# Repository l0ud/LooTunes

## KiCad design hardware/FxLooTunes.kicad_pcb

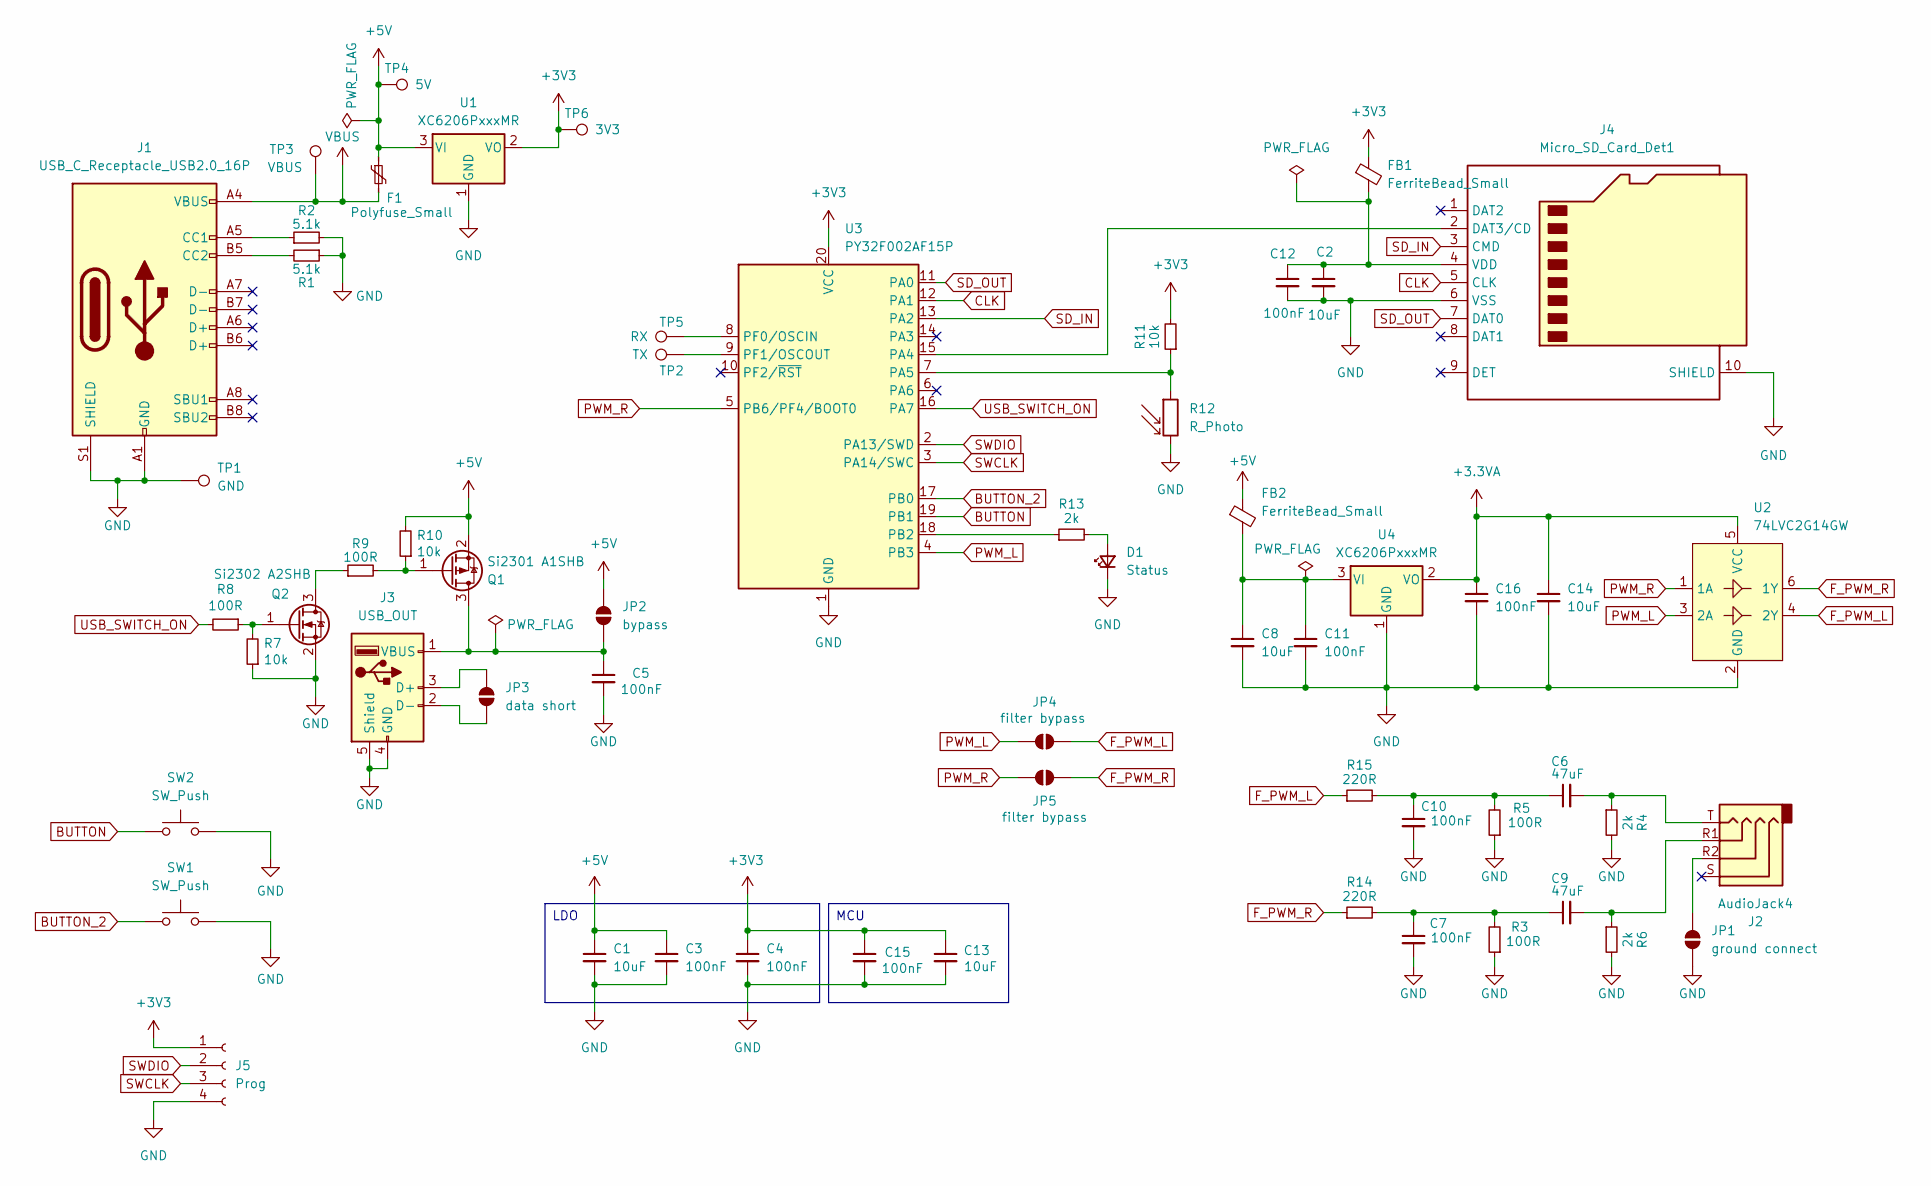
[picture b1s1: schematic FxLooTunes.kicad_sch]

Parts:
C1, C2, C8, C13, C14: 10uF; C_0402_1005Metric
C3, C4, C5, C7, C10, C11, C12, C15, C16: 100nF; C_0402_1005Metric
C6, C9: 47uF; C_0805_2012Metric
D1: Status; LED_0402_1005Metric
F1: Polyfuse_Small; Fuse_1206_3216Metric
FB1, FB2: FerriteBead_Small; L_0603_1608Metric
J1: USB_C_Receptacle_USB2.0_16P; USB_C_Receptacle_HCTL_HC-TYPE-C-16P-01A
J2: AudioJack4; PJ-322
J3: USB_OUT; USB_A_Connfly_DS1095
J4: Micro_SD_Card_Det1; GCT-MEM2055-00-190-01-A
J5: Prog; PinHeader_1x04_P1.27mm_Vertical
JP1: ground connect; SolderJumper-2_P1.3mm_Open_TrianglePad1.0x1.5mm
JP2: bypass; SolderJumper-2_P1.3mm_Open_TrianglePad1.0x1.5mm
JP3: data short; SolderJumper-2_P1.3mm_Open_TrianglePad1.0x1.5mm
JP4, JP5: filter bypass; SolderJumper-2_P1.3mm_Open_TrianglePad1.0x1.5mm
Q1: Si2301 A1SHB; SOT-23
Q2: Si2302 A2SHB; SOT-23
R1, R2: 5.1k; R_0402_1005Metric
R3, R5, R8, R9: 100R; R_0402_1005Metric
R4, R6, R13: 2k; R_0402_1005Metric
R7, R10, R11: 10k; R_0402_1005Metric
R12: R_Photo; R_LDR_5.0x4.1mm_P3mm_Vertical
R14, R15: 220R; R_0402_1005Metric
SW1, SW2: SW_Push; SW_SPST_TL3342
TP1: GND; TestPoint_Pad_D1.5mm
TP2: TX; TestPoint_Pad_D1.5mm
TP3: VBUS; TestPoint_Pad_D1.5mm
TP4: 5V; TestPoint_Pad_D1.5mm
TP5: RX; TestPoint_Pad_D1.5mm
TP6: 3V3; TestPoint_Pad_D1.5mm
U1, U4: XC6206PxxxMR; SOT-23-3
U2: 74LVC2G14GW; SOT-363_SC-70-6
U3: PY32F002AF15P; TSSOP-20_4.4x6.5mm_P0.65mm

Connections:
+3.3VA: C14.1, C16.1, U2.5 (VCC), U4.2 (VO)
+3V3: C4.1, C13.1, C15.1, FB1.1, J5.1, R11.2, TP6.1, U1.2 (VO), U3.20 (VCC)
BUTTON: SW2.1, U3.19 (PB1)
BUTTON_2: SW1.1, U3.17 (PB0)
CLK: J4.5 (CLK), U3.12 (PA1)
F_PWM_L: JP4.2 (B), R15.1, U2.4 (2Y)
F_PWM_R: JP5.2 (B), R14.1, U2.6 (1Y)
GND: C1.2, C2.2, C3.2, C4.2, C5.2, C7.2, C8.2, C10.2, C11.2, C12.2, C13.2, C14.2, C15.2, C16.2, D1.1 (K), J1.A1 (GND), J1.A12 (GND), J1.B1 (GND), J1.B12 (GND), J1.S1 (SHIELD), J3.4 (GND), J3.5 (Shield), J4.6 (VSS), J4.10 (SHIELD), J5.4, JP1.2 (B), Q2.2 (S), R1.1, R2.2, R3.1, R4.2, R5.1, R6.2, R7.1, R12.2, SW1.2, SW2.2, TP1.1, U1.1 (GND), U2.2 (GND), U3.1 (GND), U4.1 (GND)
unnamed: C6.1, C10.1, R5.2, R15.2
unnamed: C6.2, J2.T, R4.1
unnamed: C7.1, C9.1, R3.2, R14.2
unnamed: C9.2, J2.R1, R6.1
unnamed: D1.2 (A), R13.2
unnamed: J1.A5 (CC1), R2.1
unnamed: J1.B5 (CC2), R1.2
unnamed: J3.3 (D+), JP3.1 (A)
unnamed: J3.2 (D-), JP3.2 (B)
unnamed: J4.2 (DAT3/CD), U3.15 (PA4)
unnamed: C2.1, C12.1, FB1.2, J4.4 (VDD)
unnamed: J2.R2, JP1.1 (A)
unnamed: Q2.3 (D), R9.1
unnamed: Q2.1 (G), R7.2, R8.1
unnamed: Q1.1 (G), R9.2, R10.1
unnamed: R11.1, R12.1, U3.7 (PA5)
unnamed: R13.1, U3.18 (PB2)
unnamed: TP5.1, U3.8 (PF0/OSCIN)
unnamed: TP2.1, U3.9 (PF1/OSCOUT)
PWM_L: JP4.1 (A), U2.3 (2A), U3.4 (PB3)
PWM_R: JP5.1 (A), U2.1 (1A), U3.5 (PB6/PF4/BOOT0)
SD_IN: J4.3 (CMD), U3.13 (PA2)
SD_OUT: J4.7 (DAT0), U3.11 (PA0)
SWCLK: J5.3, U3.3 (PA14/SWC)
SWDIO: J5.2, U3.2 (PA13/SWD)
USB_SWITCH_IN: R8.2, U3.16 (PA7)
VBUS: F1.2, J1.A4 (VBUS), J1.A9 (VBUS), J1.B4 (VBUS), J1.B9 (VBUS), TP3.1

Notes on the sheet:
LDO
MCU

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
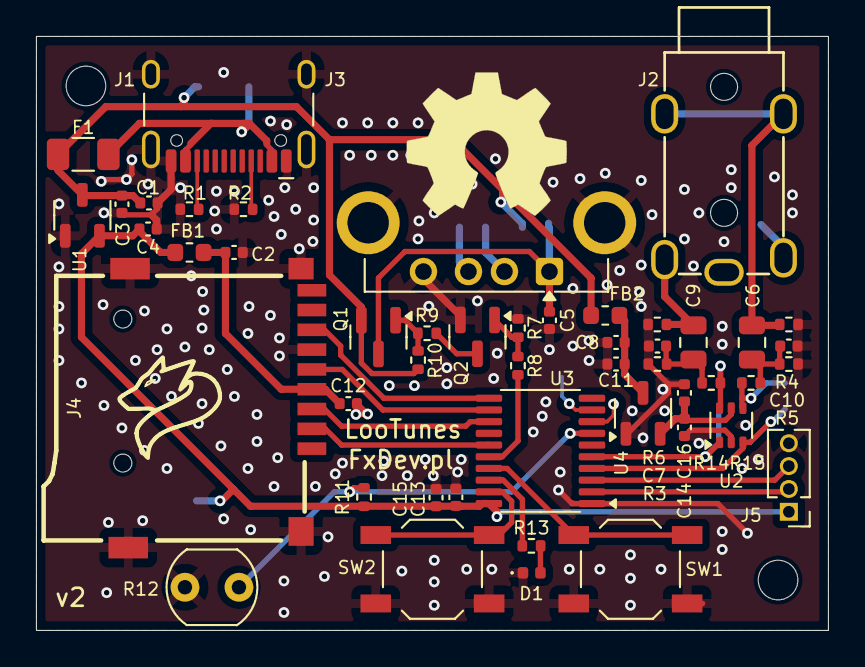
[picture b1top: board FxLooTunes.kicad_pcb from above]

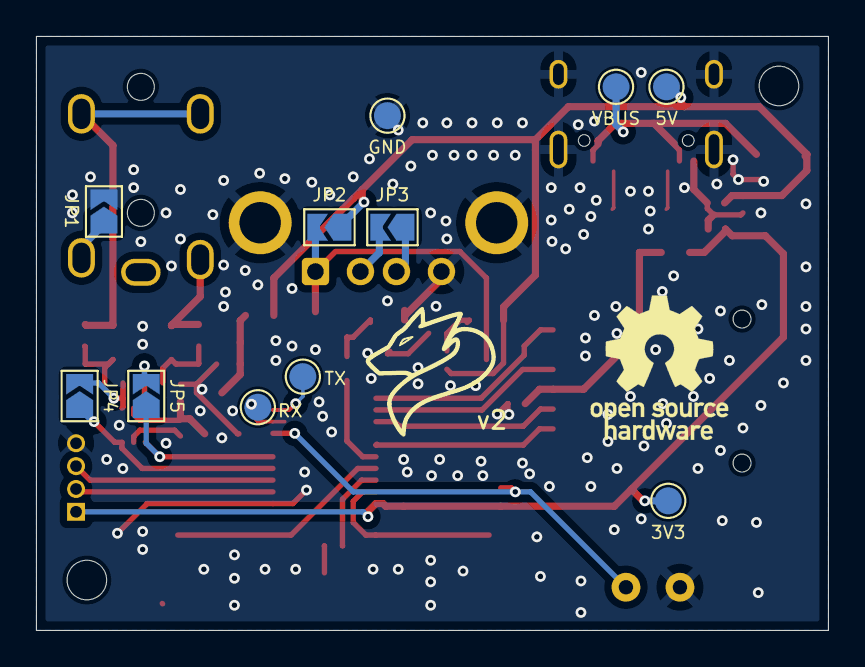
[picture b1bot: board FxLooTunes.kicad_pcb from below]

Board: 2 copper layers, 44.0 x 33.0 mm, 59 parts (11 on the bottom side), 38 nets.

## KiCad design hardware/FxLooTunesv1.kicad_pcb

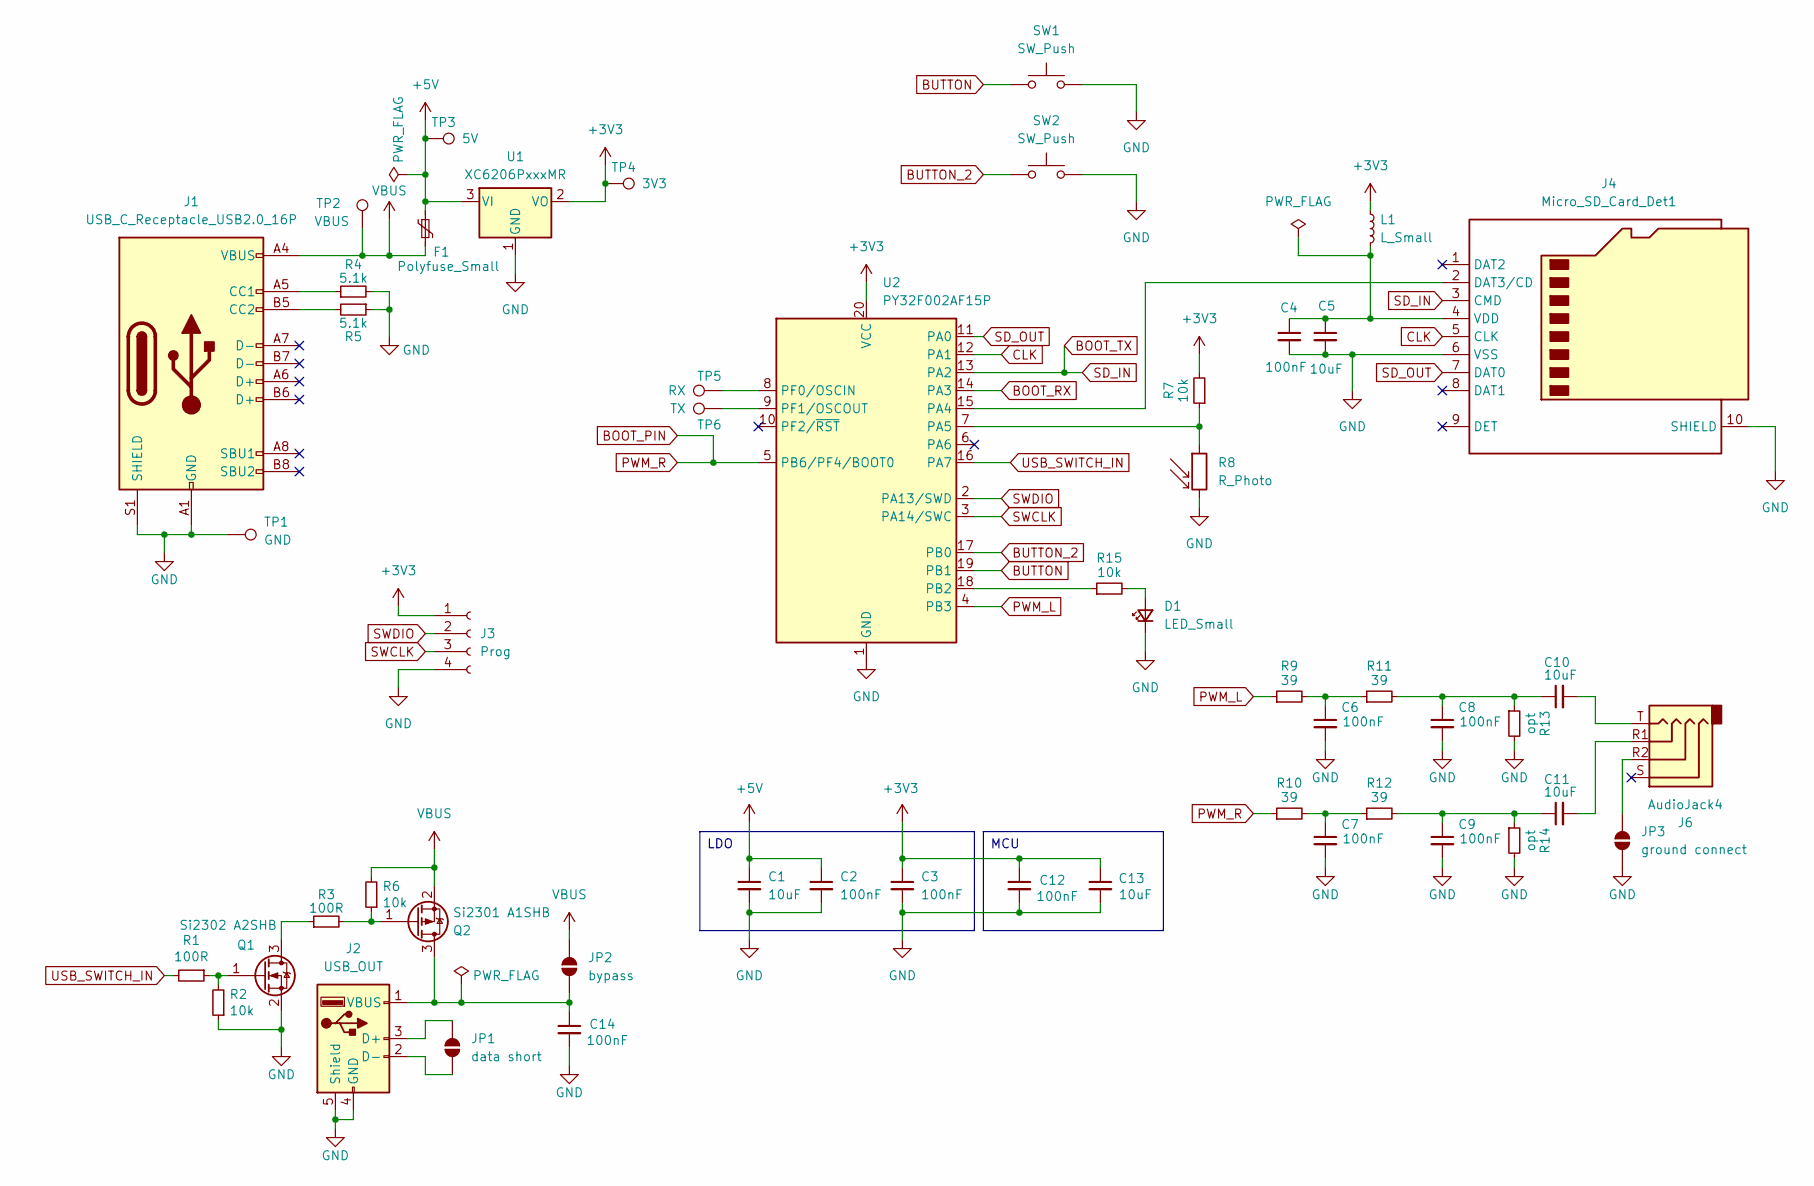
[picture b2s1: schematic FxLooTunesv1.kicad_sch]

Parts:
C1, C5, C10, C11, C13: 10uF; C_0402_1005Metric
C2, C3, C4, C6, C7, C8, C9, C12, C14: 100nF; C_0402_1005Metric
D1: LED_Small; LED_0402_1005Metric
F1: Polyfuse_Small; Fuse_1206_3216Metric
J1: USB_C_Receptacle_USB2.0_16P; USB_C_Receptacle_HCTL_HC-TYPE-C-16P-01A
J2: USB_OUT; USB_A_Connfly_DS1095
J3: Prog; PinHeader_1x04_P1.27mm_Vertical
J4: Micro_SD_Card_Det1; GCT-MEM2055-00-190-01-A
J6: AudioJack4; PJ-322
JP1: data short; SolderJumper-2_P1.3mm_Open_TrianglePad1.0x1.5mm
JP2: bypass; SolderJumper-2_P1.3mm_Open_TrianglePad1.0x1.5mm
JP3: ground connect; SolderJumper-2_P1.3mm_Open_TrianglePad1.0x1.5mm
L1: L_Small; L_0402_1005Metric
Q1: Si2302 A2SHB; SOT-23
Q2: Si2301 A1SHB; SOT-23
R1, R3: 100R; R_0402_1005Metric
R2, R6, R7, R15: 10k; R_0402_1005Metric
R4, R5: 5.1k; R_0402_1005Metric
R8: R_Photo; R_LDR_5.0x4.1mm_P3mm_Vertical
R9, R10, R11, R12: 39; R_0402_1005Metric
R13, R14: opt; R_0402_1005Metric
SW1, SW2: SW_Push; SW_SPST_TL3342
TP1: GND; TestPoint_Pad_D1.5mm
TP2: VBUS; TestPoint_Pad_D1.5mm
TP3: 5V; TestPoint_Pad_D1.5mm
TP4: 3V3; TestPoint_Pad_D1.5mm
TP5: RX; TestPoint_Pad_D1.5mm
TP6: TX; TestPoint_Pad_D1.5mm
U1: XC6206PxxxMR; SOT-23-3
U2: PY32F002AF15P; TSSOP-20_4.4x6.5mm_P0.65mm

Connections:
+3V3: C3.1, C12.1, C13.1, J3.1, L1.1, R7.2, TP4.1, U1.2 (VO), U2.20 (VCC)
BOOT_PIN: R10.1, U2.5 (PB6/PF4/BOOT0)
BOOT_RX: U2.14 (PA3)
BOOT_TX: J4.3 (CMD), U2.13 (PA2)
BUTTON: SW1.1, U2.19 (PB1)
BUTTON_2: SW2.1, U2.17 (PB0)
CLK: J4.5 (CLK), U2.12 (PA1)
GND: C1.2, C2.2, C3.2, C4.2, C5.2, C6.2, C7.2, C8.2, C9.2, C12.2, C13.2, C14.2, D1.1 (K), J1.A1 (GND), J1.A12 (GND), J1.B1 (GND), J1.B12 (GND), J1.S1 (SHIELD), J2.4 (GND), J2.5 (Shield), J3.4, J4.6 (VSS), J4.10 (SHIELD), JP3.2 (B), Q1.2 (S), R2.1, R4.2, R5.1, R8.2, R13.2, R14.2, SW1.2, SW2.2, TP1.1, U1.1 (GND), U2.1 (GND)
unnamed: C6.1, R9.2, R11.1
unnamed: C7.1, R10.2, R12.1
unnamed: C8.1, C10.1, R11.2, R13.1
unnamed: C10.2, J6.T
unnamed: C9.1, C11.1, R12.2, R14.1
unnamed: C11.2, J6.R1
unnamed: D1.2 (A), R15.2
unnamed: J1.A5 (CC1), R4.1
unnamed: J1.B5 (CC2), R5.2
unnamed: J2.3 (D+), JP1.1 (A)
unnamed: J2.2 (D-), JP1.2 (B)
unnamed: J4.2 (DAT3/CD), U2.15 (PA4)
unnamed: C4.1, C5.1, J4.4 (VDD), L1.2
unnamed: J6.R2, JP3.1 (A)
unnamed: Q1.3 (D), R3.1
unnamed: Q1.1 (G), R1.1, R2.2
unnamed: Q2.1 (G), R3.2, R6.1
unnamed: R7.1, R8.1, U2.7 (PA5)
unnamed: R15.1, U2.18 (PB2)
unnamed: TP5.1, U2.8 (PF0/OSCIN)
unnamed: TP6.1, U2.9 (PF1/OSCOUT)
PWM_L: R9.1, U2.4 (PB3)
SD_OUT: J4.7 (DAT0), U2.11 (PA0)
SWCLK: J3.3, U2.3 (PA14/SWC)
SWDIO: J3.2, U2.2 (PA13/SWD)
USB_SWITCH_IN: R1.2, U2.16 (PA7)
VBUS: F1.2, J1.A4 (VBUS), J1.A9 (VBUS), J1.B4 (VBUS), J1.B9 (VBUS), JP2.1 (A), Q2.2 (S), R6.2, TP2.1

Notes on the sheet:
LDO
MCU

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
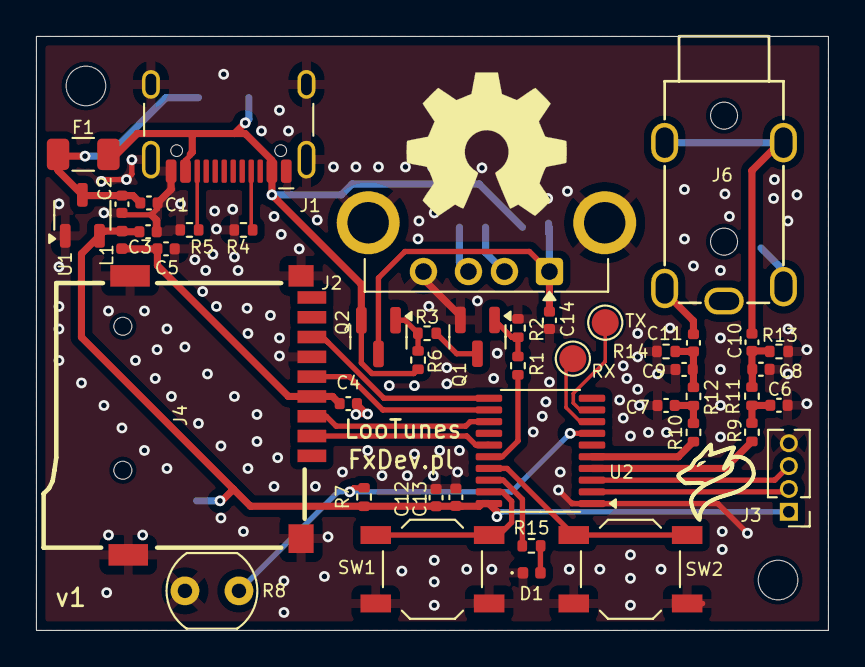
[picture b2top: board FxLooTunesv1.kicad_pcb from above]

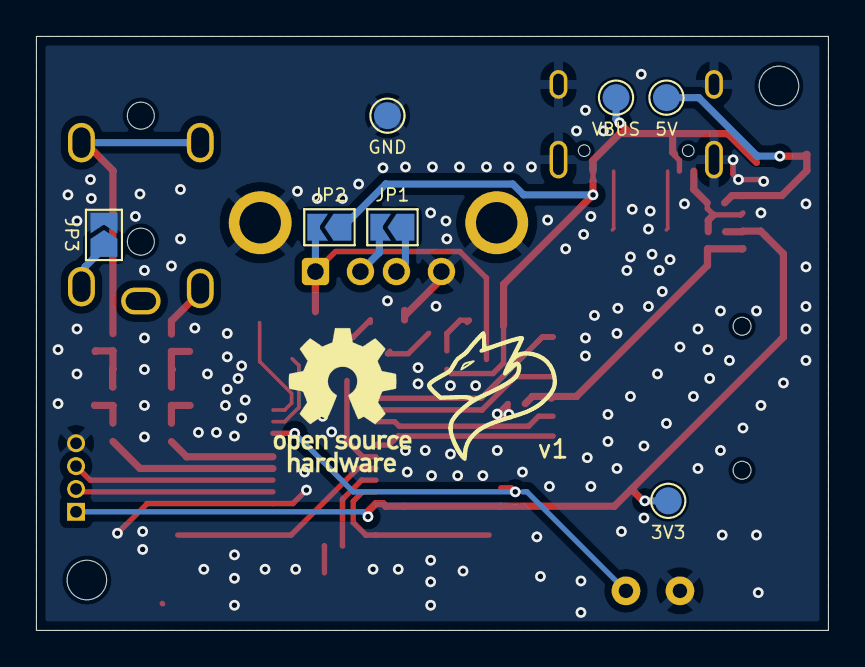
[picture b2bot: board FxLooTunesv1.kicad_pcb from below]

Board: 2 copper layers, 44.0 x 33.0 mm, 52 parts (7 on the bottom side), 36 nets.

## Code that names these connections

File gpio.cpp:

#include "gpio.h"

void GPIO::init() {
    __HAL_RCC_GPIOA_CLK_ENABLE();
    __HAL_RCC_GPIOB_CLK_ENABLE();

    // PA4 - SD NSS
    GPIOA->MODER &= ~GPIO_MODER_MODE4_Msk;
    GPIOA->MODER |= GPIO_MODER_MODE4_0; // output mode
    GPIOA->OTYPER &= ~GPIO_OTYPER_OT4_Msk; // push-pull
    GPIOA->OSPEEDR &= ~GPIO_OSPEEDR_OSPEED4_Msk;
    GPIOA->OSPEEDR |= GPIO_OSPEEDR_OSPEED4_1 | GPIO_OSPEEDR_OSPEED4_0; // very high speed

    GPIOA->BSRR = GPIO_BSRR_BS4;

    // PA5 - light sensor (ADC_IN5)
    GPIOA->MODER &= ~GPIO_MODER_MODE5_Msk; // clear mode
    GPIOA->MODER |= GPIO_MODER_MODE5_0 | GPIO_MODER_MODE5_1; // analog mode
    GPIOA->OTYPER &= ~GPIO_OTYPER_OT5_Msk; // push-pull
    GPIOA->OSPEEDR &= ~GPIO_OSPEEDR_OSPEED5_Msk; // low speed (00)

    // PA7 - USB power pin (output)
    GPIOA->MODER &= ~GPIO_MODER_MODE7_Msk;
    GPIOA->MODER |= GPIO_MODER_MODE7_0; // output mode
    GPIOA->OTYPER &= ~GPIO_OTYPER_OT7_Msk; // push-pull
    GPIOA->OSPEEDR &= ~GPIO_OSPEEDR_OSPEED7_Msk;
    GPIOA->OSPEEDR |= GPIO_OSPEEDR_OSPEED7_0; // low speed (01)
    // turn off USB power
    GPIOA->BSRR = GPIO_BSRR_BR7; // reset PA7

    // PB2 - led pin, GPIO output
    GPIOB->MODER &= ~GPIO_MODER_MODE2_Msk;
    GPIOB->MODER |= GPIO_MODER_MODE2_0; // output mode
    GPIOB->OTYPER &= ~GPIO_OTYPER_OT2_Msk; // push-pull
    GPIOB->OSPEEDR &= ~GPIO_OSPEEDR_OSPEED2_Msk;
    GPIOB->OSPEEDR |= GPIO_OSPEEDR_OSPEED2_0; // low speed (01)

    // PB3 - TIM1_CH2 for audio
    GPIOB->MODER &= ~GPIO_MODER_MODE3_Msk;
    GPIOB->MODER |= GPIO_MODER_MODE3_1; // alternate mode
    GPIOB->AFR[0] |= (1 << GPIO_AFRL_AFSEL3_Pos); // AF1: TIM1_CH2

    // PB6 - TIM1_CH3 for audio
    GPIOB->MODER &= ~GPIO_MODER_MODE6_Msk;
    GPIOB->MODER |= GPIO_MODER_MODE6_1; // alternate mode
    GPIOB->AFR[0] |= (1 << GPIO_AFRL_AFSEL6_Pos); // AF1: TIM1_CH3
}

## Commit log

2025-08-04 working sbc player with light detection and button support
2025-08-22 optimization: cache cluster ranges for playback. Less popping with marginally slower SDs
2025-08-24 optimization: use SD card as ram, prefetching next sector
2025-08-24 optimization: use CMD18 for sector ranges. All my cards seems compatible now
2025-08-24 insert padding after non-data command for some SDs. Do not reinitialize fs on main.
2025-09-05 directory support, changed flow to handle errors better, faster file opening, plans for new config params.
2025-09-09 random playback with position save WIP, buggy
2025-09-13 added missing files, try to split sequencial and random playback
2025-09-15 state saving, refactoring of playback
2025-09-16 fix light thresholds
2025-09-16 off-by-one bugfix, state should not accumulate increasing dir number, some simplifications
2025-09-17 apply seed from config, or make it randomized
2025-09-17 cleanup
2025-09-17 mute on state dump
2025-09-21 typo fix in config template
2025-10-03 test: 10bit audio in the cost of lower (22kHz) pwm carrier
2025-10-03 split playback to separate files
2025-10-06 fade in and fade out support. Simplification: never actually stop pwm to avoid popping noise
2025-10-09 fix undefined startup state
2025-10-10 do not save state during playback (when not muted). Eliminate pops after mode button press
2025-10-12 add missing petitfat license
2025-10-13 add license and headers
2025-10-13 remove defines.h
2025-10-17 cleanup comments, move libsbc to main repo
2025-10-19 move firmware into firmware dir, sd contents into sd
2025-10-19 remove redundant files and libs
2025-10-19 add hardware dir, removed gui accidently copy pasted from other project
2025-10-20 cleanup and modernize config reader. Fix project name and workspace settings
2025-10-20 minor cleanup
2025-10-21 add support for standard capacity cards
2025-11-15 update schematics, remove watchdog remainings and workarounds
2025-11-18 bugfix: do not start from fade-out on power on
2025-11-18 add some assets
2025-11-18 SD card folder
